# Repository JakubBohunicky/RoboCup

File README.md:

# RoboCup Junior Soccer

These are all the RoboCupJunior Soccer robots I built with my team, from our first Arduino Mega robot in 2024
to the two ESP32-S3 robots we took to the 2026 world final in Incheon.

| Folder | Event | Robot |
|---|---|---|
| [`2026_Korea/`](2026_Korea) | **RoboCup 2026 world final, Incheon: 11th of 24** | ESP32-S3, Maxon/ESCON drive, 48 line sensors, ESP-NOW role swapping ([write-up](https://developer.espressif.com/blog/2026/09/robocup-junior-soccer-robot/)) |
| [`2026_Slovakia/`](2026_Slovakia) | 2026 Slovak championship, 2nd place | Arduino Mega, gen 2 of the Bari robot |
| [`2025_Bari/`](2025_Bari) | RoboCup 2025, Bari | Arduino Mega, gen 1 |
| [`2024/`](2024) | RoboCup 2024, team XLC-Captur | Arduino Mega, our first robot |

**[2026_Korea](2026_Korea)** is the one we're proudest of.

Released under the [MIT License](LICENSE).

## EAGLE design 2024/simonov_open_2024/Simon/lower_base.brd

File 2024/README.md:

# RoboCupJunior Soccer 2024 — team XLC-Captur

This was our first RoboCupJunior Soccer robot. We built it around an **Arduino Mega**, with a BNO055
compass, a Pixy2 camera to find the goals, an SSD1306 display and a ring of TSOP IR receivers to find
the ball. We designed the electronics as three Eagle boards: a lower base, an upper base and the TSOP
sensor ring.

The firmware grew one sketch at a time, from `Code/MainCodeV1` to `Code/mainCodeV10`, which is the version
we ended with. Before putting each part into the main code, we tried it in a small sketch first: compass
rotation, dribbler, kicker, IR ball sensors and the Pixy. Those sketches are in `Code/test_code/`.

| Folder | Contents |
|---|---|
| `Code/` | Main firmware V1–V10 and the test sketches |
| `PCBs/` | Eagle schematics and boards |
| `Photo/` | Renders of the three boards |
| `Doc/` | Our team description paper, poster and BOM |

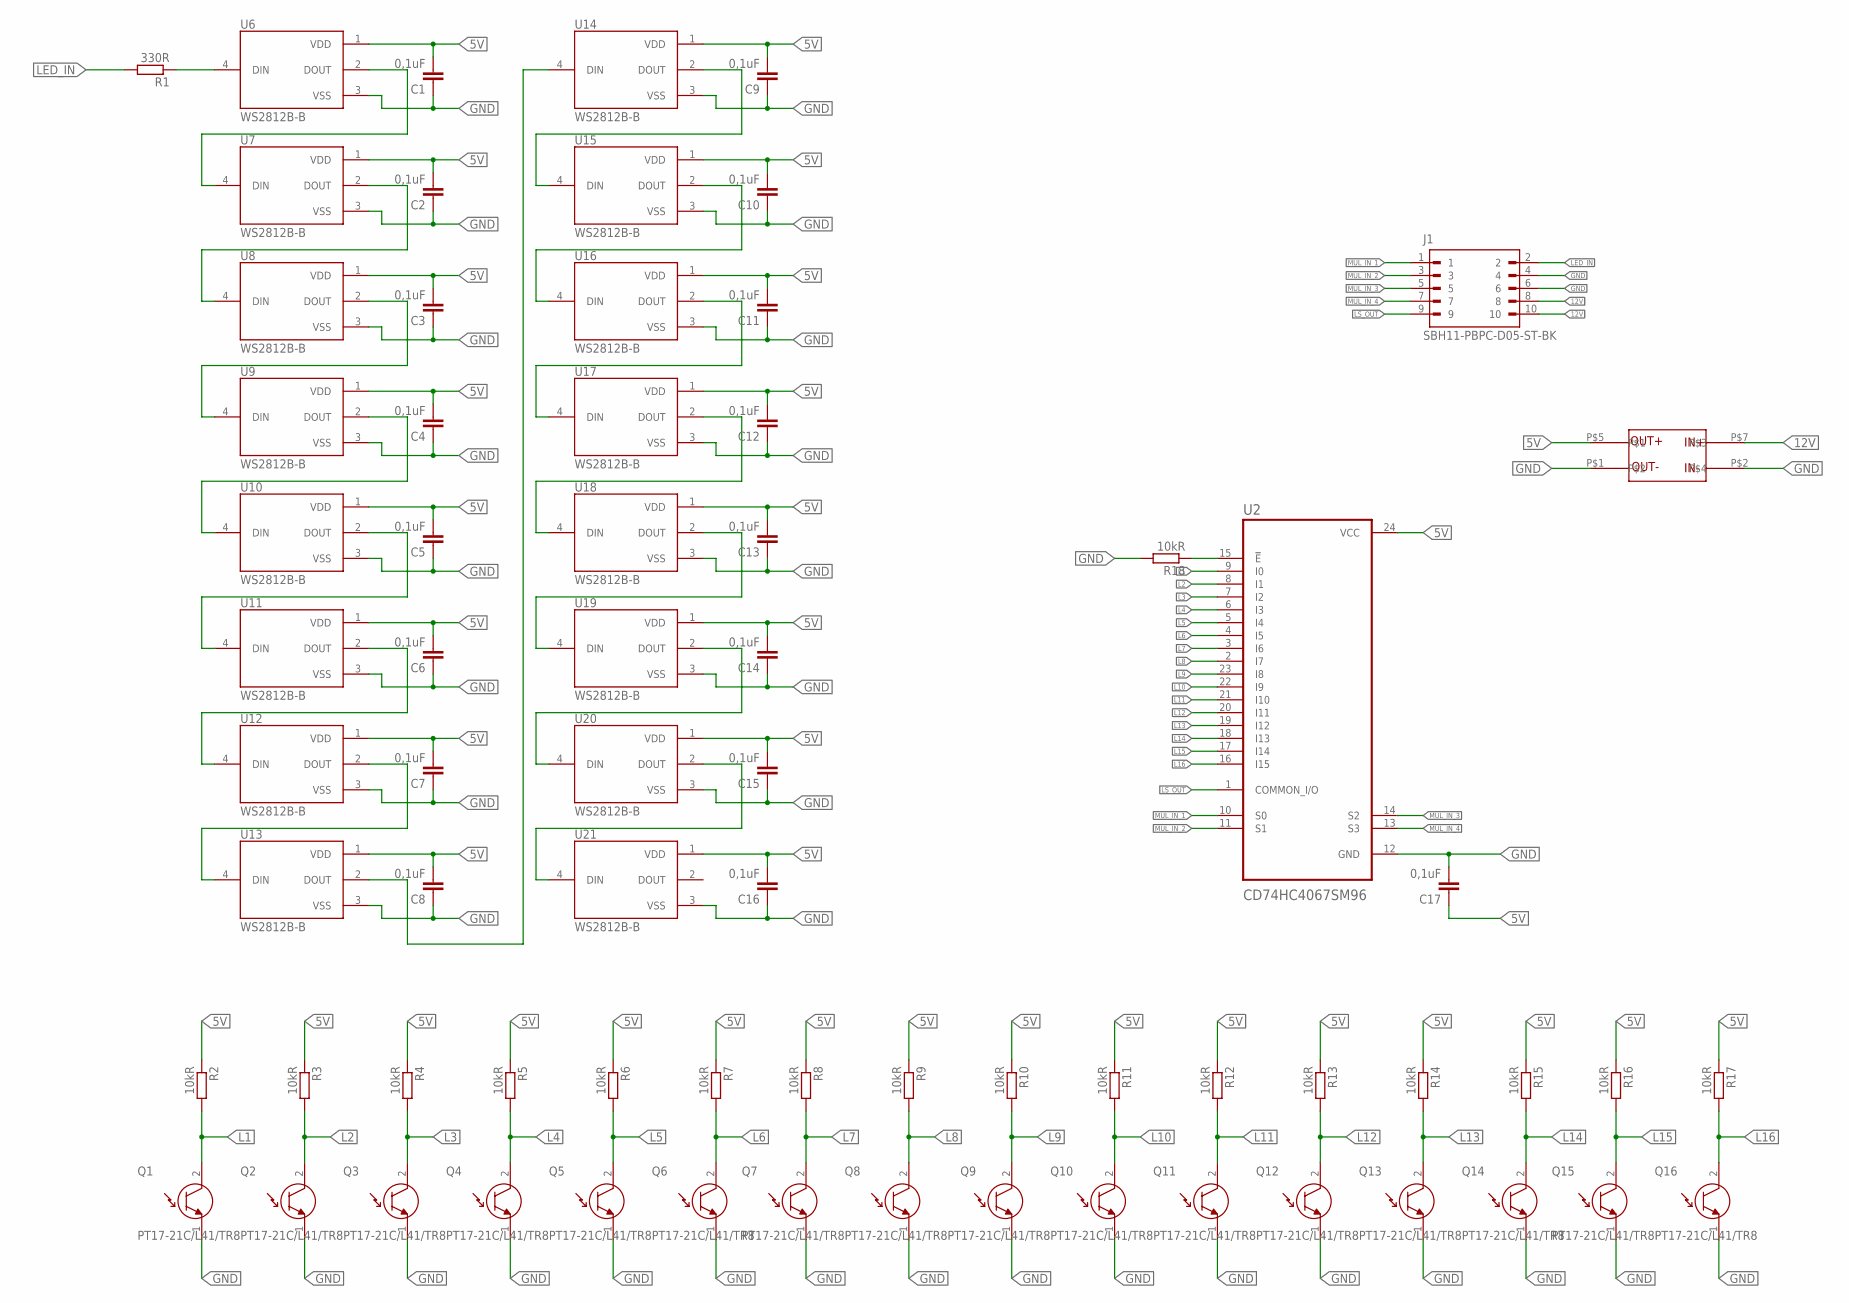
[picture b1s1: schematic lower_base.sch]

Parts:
C1, C2, C3, C4, C5, C6, C7, C8, C9, C10, C11, C12, C13, C14, C15, C16, C17: 0,1uF; C0805
J1: SBH11-PBPC-D05-ST-BK; SULLINS_SBH11-PBPC-D05-ST-BK
Q1, Q2, Q3, Q4, Q5, Q6, Q7, Q8, Q9, Q10, Q11, Q12, Q13, Q14, Q15, Q16: PT17-21C/L41/TR8; OPTO_PT17-21C/L41/TR8
R1: 330R; R0805
R2, R3, R4, R5, R6, R7, R8, R9, R10, R11, R12, R13, R14, R15, R16, R17, R18: 10kR; R0805
U2: CD74HC4067SM96; SOP65P780X200-24N
U6, U7, U8, U9, U10, U11, U12, U13, U14, U15, U16, U17, U18, U19, U20, U21: WS2812B-B; LED_WS2812B-B
U$1: REGULATOR_3A_MINI; REGULATOR_3A_MIN

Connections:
5V: C1.2, C2.2, C3.2, C4.2, C5.2, C6.2, C7.2, C8.2, C9.2, C10.2, C11.2, C12.2, C13.2, C14.2, C15.2, C16.2, C17.1, R2.1, R3.1, R4.1, R5.1, R6.1, R7.1, R8.1, R9.1, R10.1, R11.1, R12.1, R13.1, R14.1, R15.1, R16.1, R17.1, U2.24 (VCC), U6.1 (VDD), U7.1 (VDD), U8.1 (VDD), U9.1 (VDD), U10.1 (VDD), U11.1 (VDD), U12.1 (VDD), U13.1 (VDD), U14.1 (VDD), U15.1 (VDD), U16.1 (VDD), U17.1 (VDD), U18.1 (VDD), U19.1 (VDD), U20.1 (VDD), U21.1 (VDD), U$1.P$5
12V: J1.8, J1.10, U$1.P$7
GND: C1.1, C2.1, C3.1, C4.1, C5.1, C6.1, C7.1, C8.1, C9.1, C10.1, C11.1, C12.1, C13.1, C14.1, C15.1, C16.1, C17.2, J1.4, J1.6, Q1.1 (ET), Q2.1 (ET), Q3.1 (ET), Q4.1 (ET), Q5.1 (ET), Q6.1 (ET), Q7.1 (ET), Q8.1 (ET), Q9.1 (ET), Q10.1 (ET), Q11.1 (ET), Q12.1 (ET), Q13.1 (ET), Q14.1 (ET), Q15.1 (ET), Q16.1 (ET), R18.2, U2.12 (GND), U6.3 (VSS), U7.3 (VSS), U8.3 (VSS), U9.3 (VSS), U10.3 (VSS), U11.3 (VSS), U12.3 (VSS), U13.3 (VSS), U14.3 (VSS), U15.3 (VSS), U16.3 (VSS), U17.3 (VSS), U18.3 (VSS), U19.3 (VSS), U20.3 (VSS), U21.3 (VSS), U$1.P$1, U$1.P$2
L1: Q1.2 (CT), R2.2, U2.9 (I0)
L2: Q2.2 (CT), R3.2, U2.8 (I1)
L3: Q3.2 (CT), R4.2, U2.7 (I2)
L4: Q4.2 (CT), R5.2, U2.6 (I3)
L5: Q5.2 (CT), R6.2, U2.5 (I4)
L6: Q6.2 (CT), R7.2, U2.4 (I5)
L7: Q7.2 (CT), R8.2, U2.3 (I6)
L8: Q8.2 (CT), R9.2, U2.2 (I7)
L9: Q9.2 (CT), R10.2, U2.23 (I8)
L10: Q10.2 (CT), R11.2, U2.22 (I9)
L11: Q11.2 (CT), R12.2, U2.21 (I10)
L12: Q12.2 (CT), R13.2, U2.20 (I11)
L13: Q13.2 (CT), R14.2, U2.19 (I12)
L14: Q14.2 (CT), R15.2, U2.18 (I13)
L15: Q15.2 (CT), R16.2, U2.17 (I14)
L16: Q16.2 (CT), R17.2, U2.16 (I15)
LED_IN: J1.2, R1.2
LS_OUT: J1.9, U2.1 (COMMON_I/O)
MUL_IN_1: J1.1, U2.10 (S0)
MUL_IN_2: J1.3, U2.11 (S1)
MUL_IN_3: J1.5, U2.14 (S2)
MUL_IN_4: J1.7, U2.13 (S3)
unnamed: R1.1, U6.4 (DIN)
unnamed: U6.2 (DOUT), U7.4 (DIN)
unnamed: U7.2 (DOUT), U8.4 (DIN)
unnamed: U8.2 (DOUT), U9.4 (DIN)
unnamed: U9.2 (DOUT), U10.4 (DIN)
unnamed: U10.2 (DOUT), U11.4 (DIN)
unnamed: U11.2 (DOUT), U12.4 (DIN)
unnamed: U12.2 (DOUT), U13.4 (DIN)
unnamed: U13.2 (DOUT), U14.4 (DIN)
unnamed: U17.2 (DOUT), U18.4 (DIN)
unnamed: U18.2 (DOUT), U19.4 (DIN)
unnamed: U14.2 (DOUT), U15.4 (DIN)
unnamed: U15.2 (DOUT), U16.4 (DIN)
unnamed: U16.2 (DOUT), U17.4 (DIN)
unnamed: U19.2 (DOUT), U20.4 (DIN)
unnamed: U20.2 (DOUT), U21.4 (DIN)
unnamed: R18.1, U2.15 (!E)

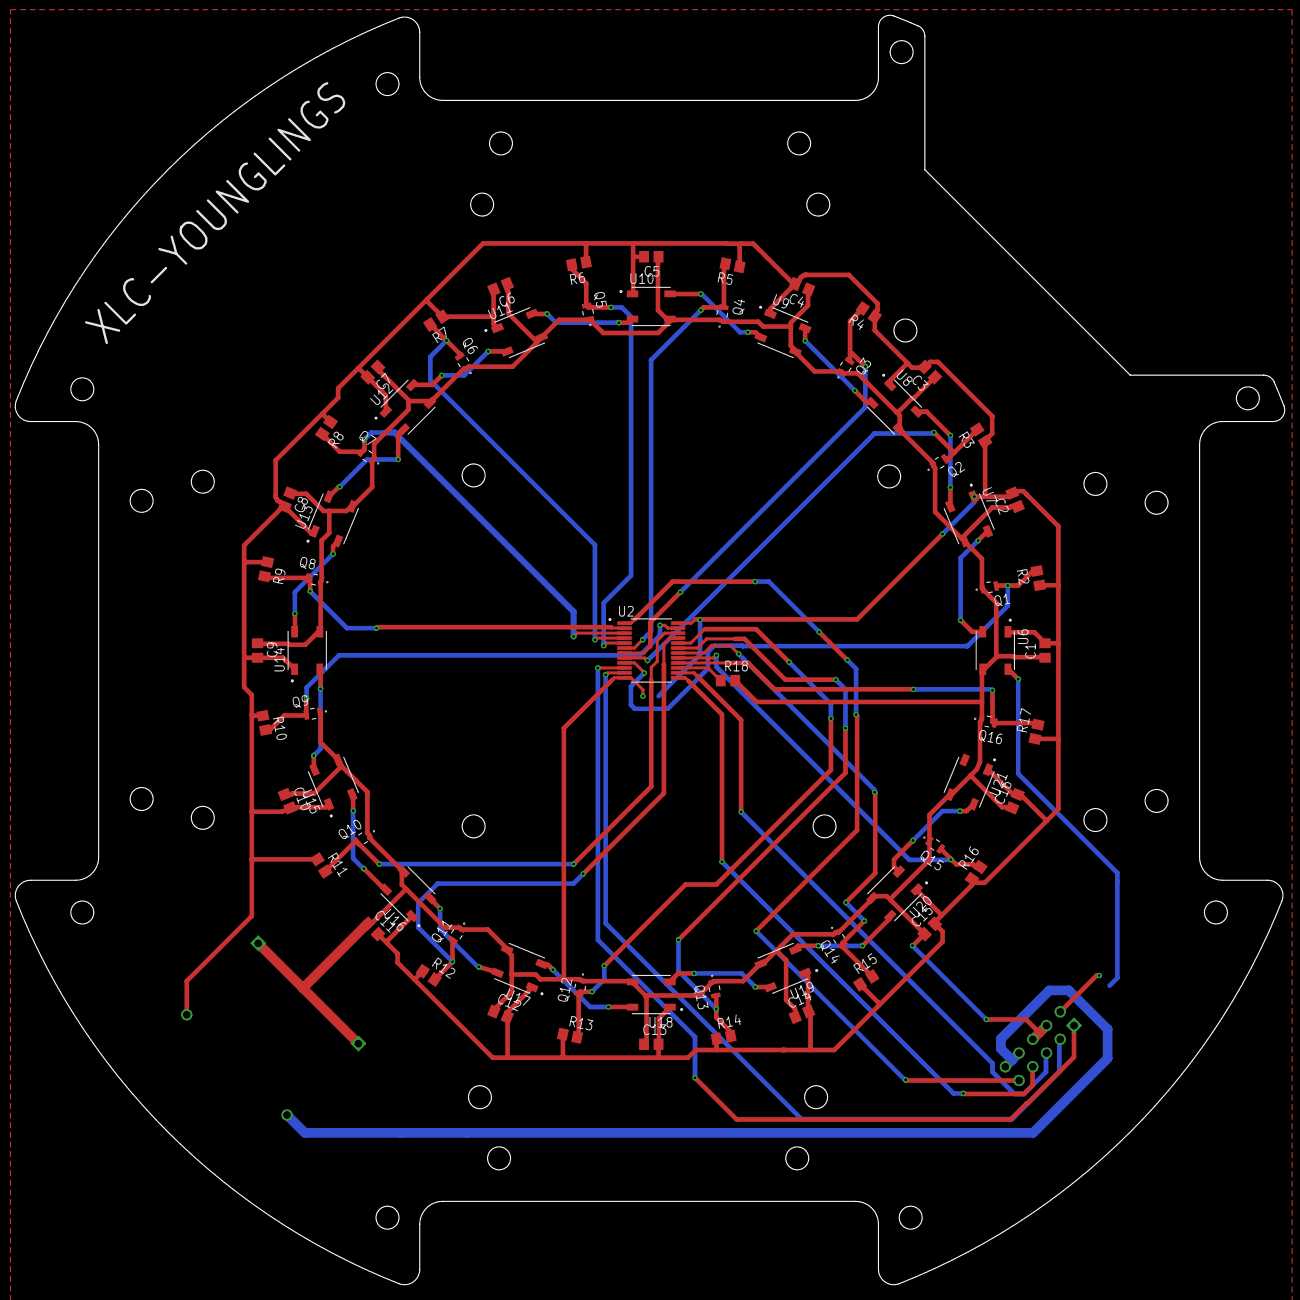
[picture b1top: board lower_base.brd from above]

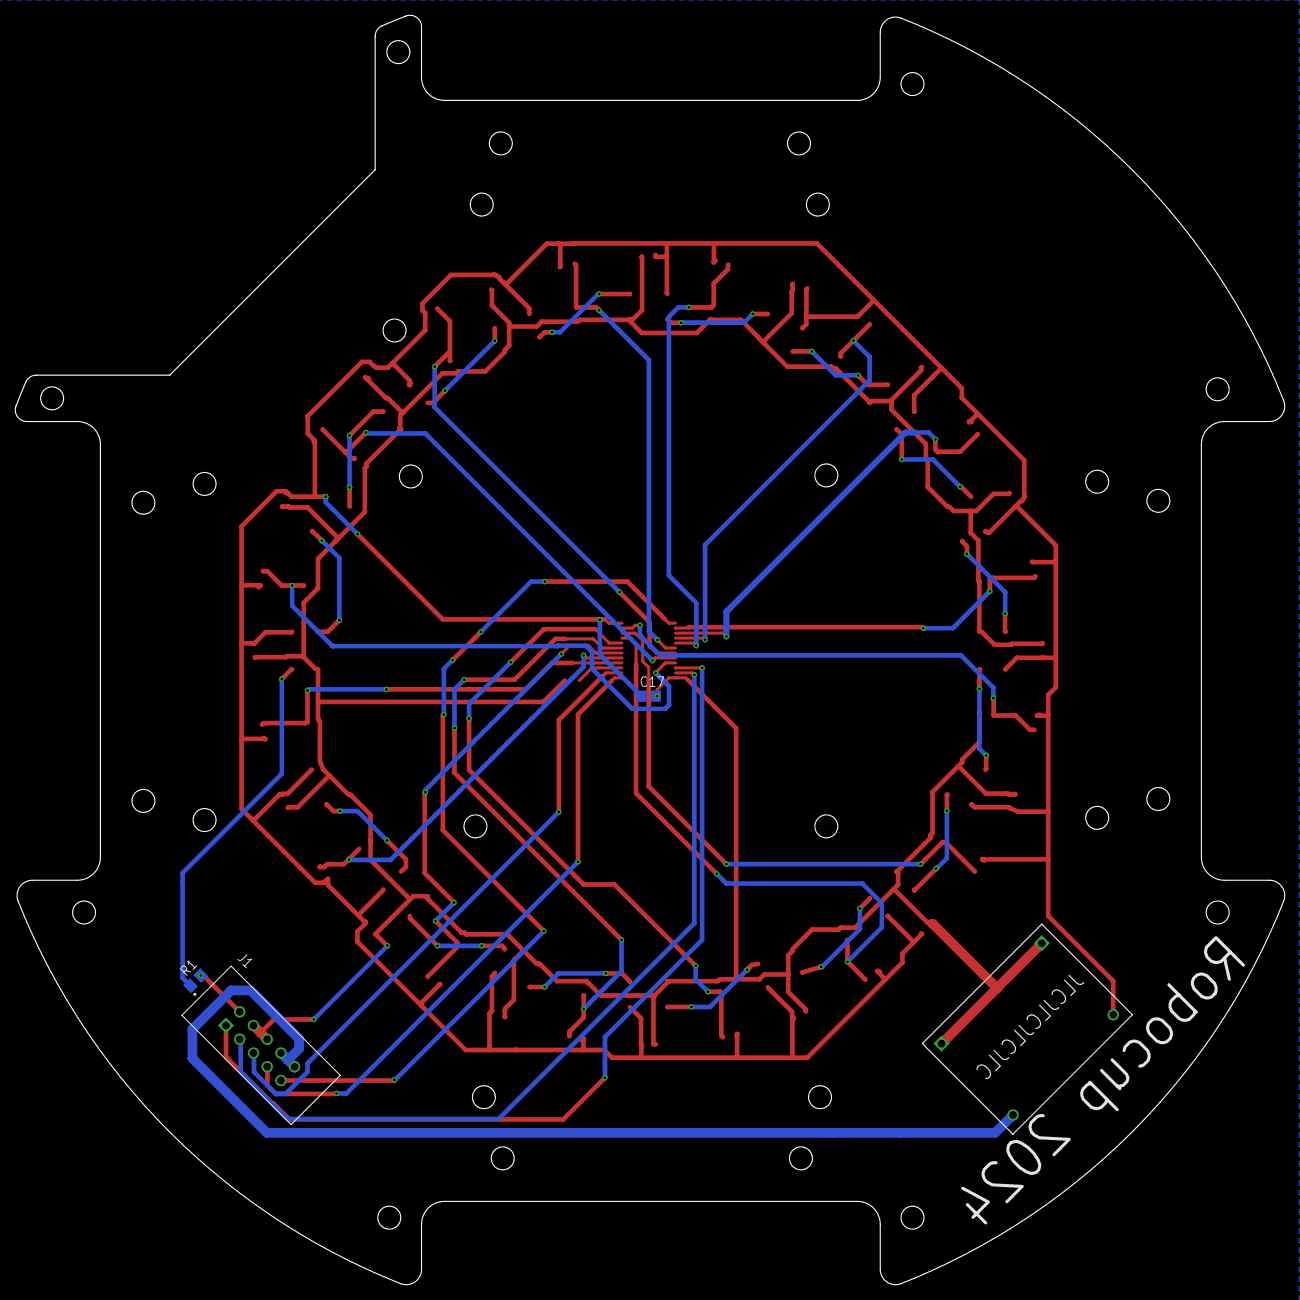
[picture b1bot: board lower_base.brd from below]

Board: 2 copper layers, 166.0 x 166.0 mm, 70 parts (4 on the bottom side), 42 nets.

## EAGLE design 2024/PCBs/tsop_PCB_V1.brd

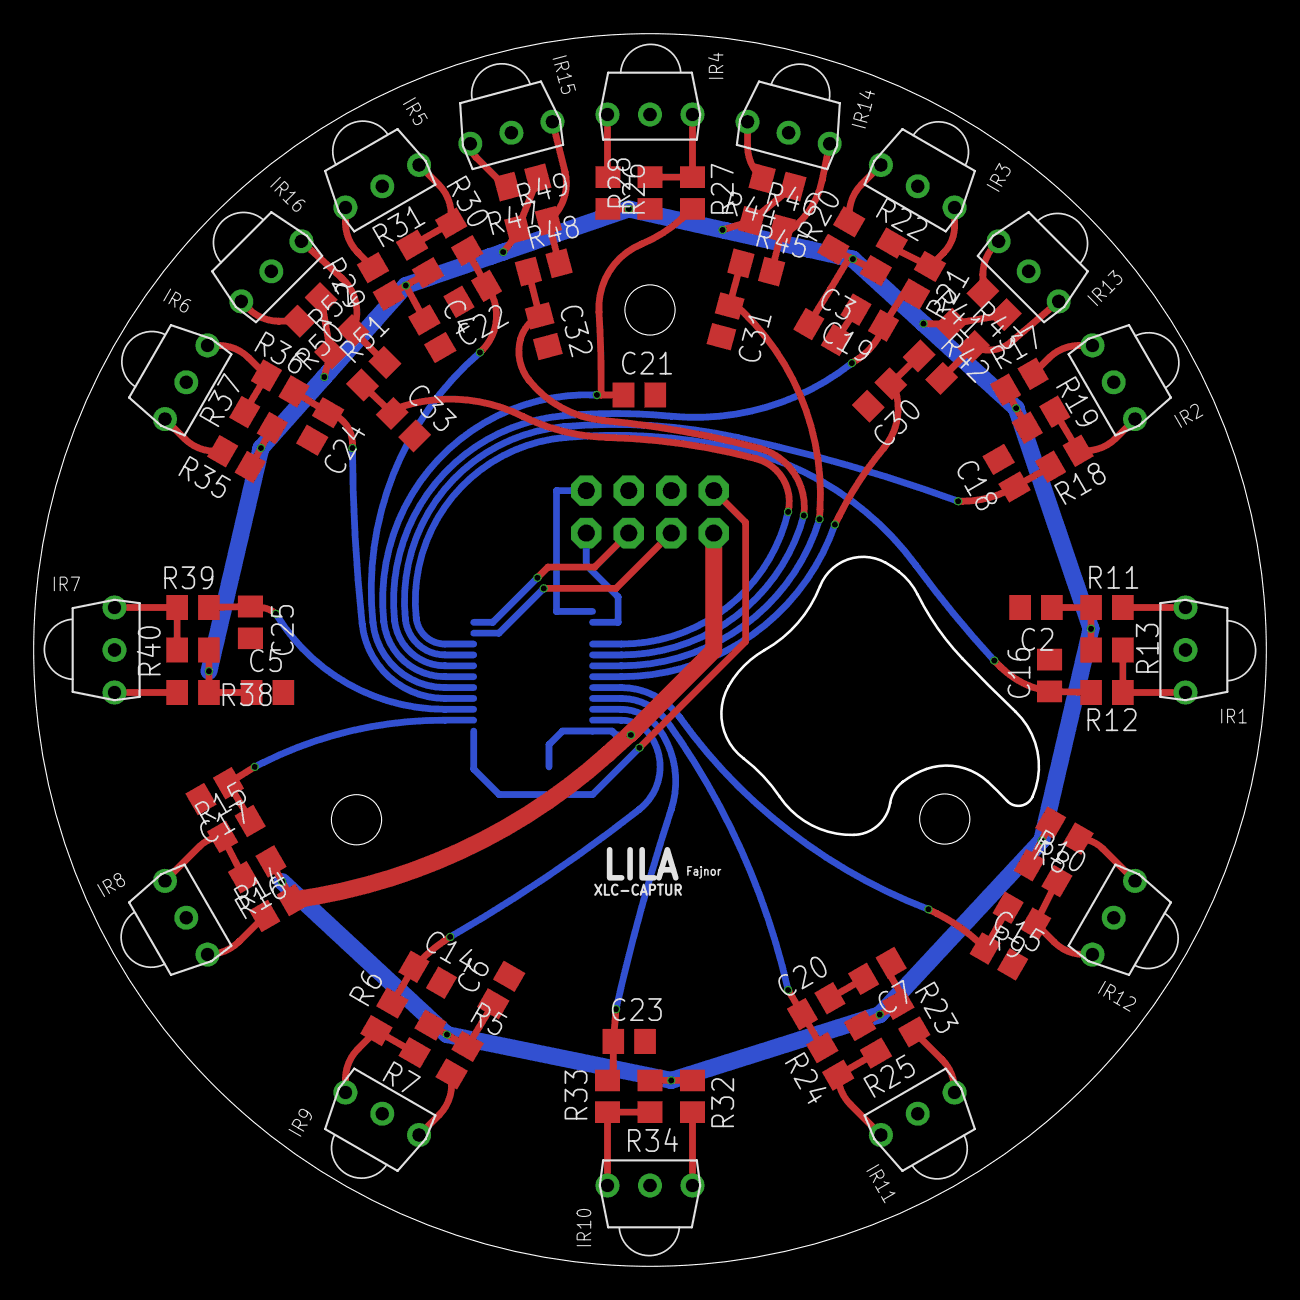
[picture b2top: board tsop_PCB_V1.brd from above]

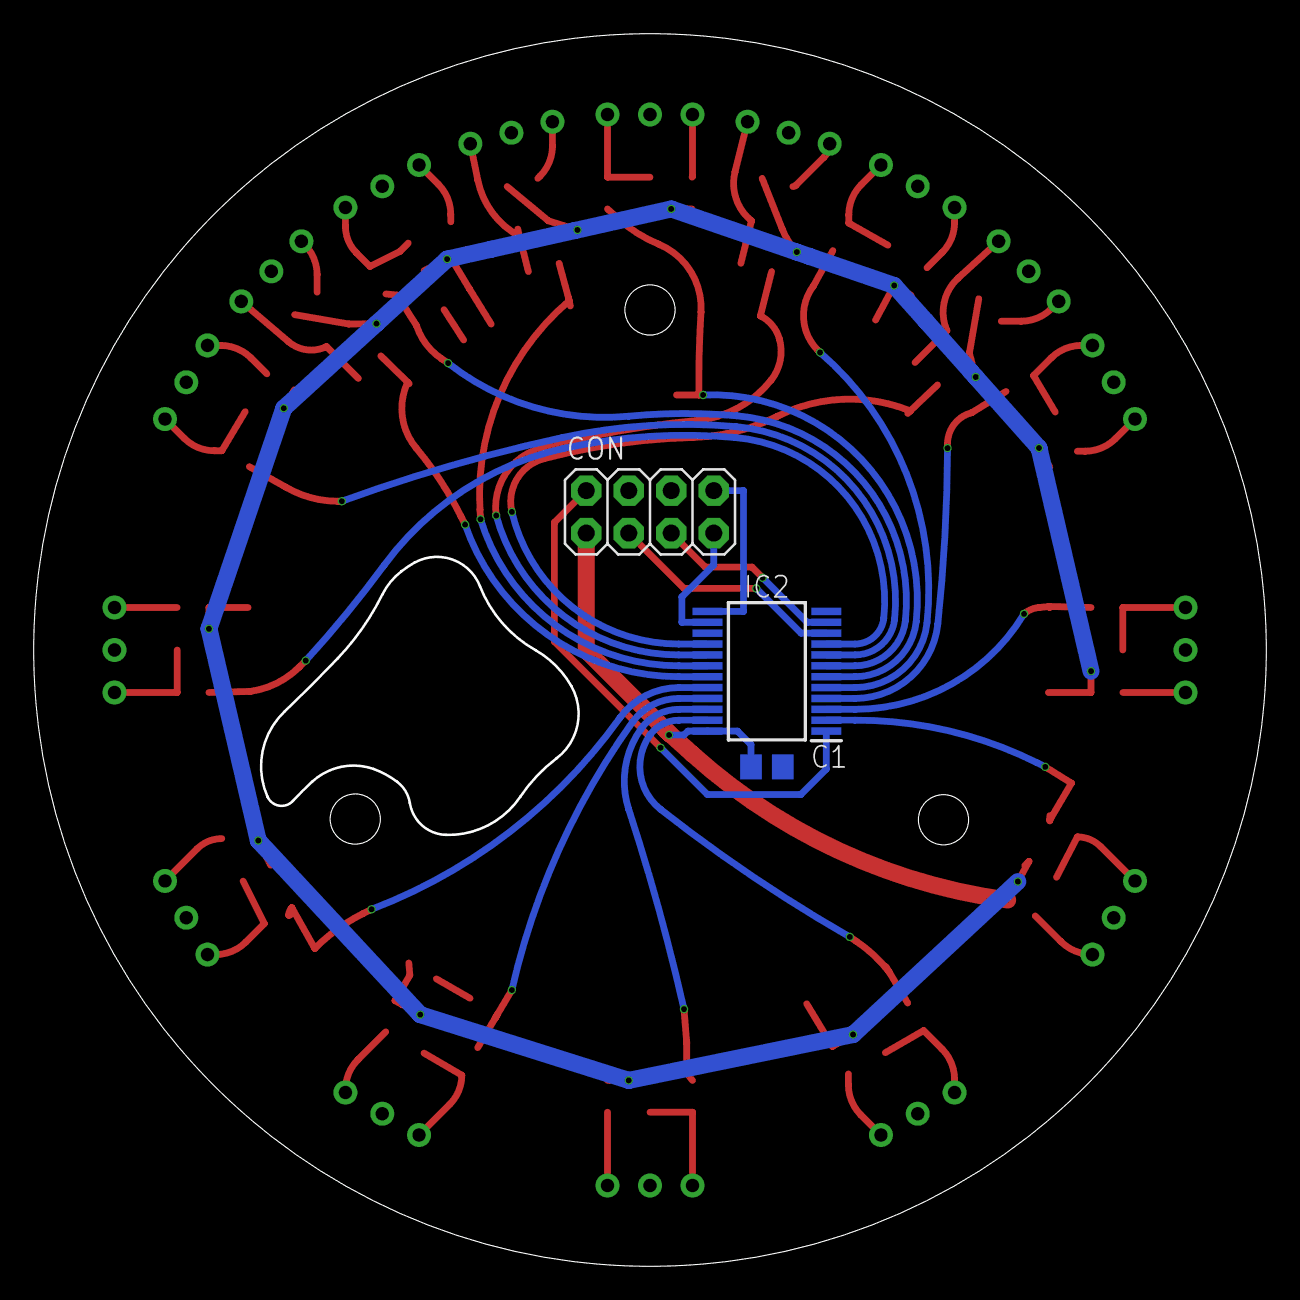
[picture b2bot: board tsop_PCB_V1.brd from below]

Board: 2 copper layers, 73.7 x 73.7 mm, 89 parts (3 on the bottom side), 55 nets.

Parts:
C1, C2, C3, C4, C5, C6, C7: 100nF; C0805
C14, C15, C16, C17, C18, C19, C20, C21, C22, C23, C24, C25, C30, C31, C32, C33: 1u; C0805
CON: 2X04
IC2: CD74HC4067SM96; SOP65P780X200-24N
IR1, IR2, IR3, IR4, IR5, IR6, IR7, IR8, IR9, IR10, IR11, IR12, IR13, IR14, IR15, IR16: TSSP58038; TSOP
R5, R8, R11, R14, R17, R20, R23, R26, R29, R32, R35, R38, R41, R44, R47, R50: 10R; R0805
R6, R9, R12, R15, R18, R21, R24, R27, R30, R33, R36, R39, R42, R45, R48, R51: 100k; R0805
R7, R10, R13, R16, R19, R22, R25, R28, R31, R34, R37, R40, R43, R46, R49, R52: 4.7k; R0805

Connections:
+5V: C1.1, C2.1, C3.1, C4.1, C5.1, C6.1, C7.1, CON.1, IC2.24, R5.1, R7.1, R8.1, R10.1, R11.1, R13.1, R14.1, R16.1, R17.1, R19.1, R20.1, R22.1, R23.1, R25.1, R26.1, R28.1, R29.1, R31.1, R32.1, R34.1, R35.1, R37.1, R38.1, R40.1, R41.1, R43.1, R44.1, R46.1, R47.1, R49.1, R50.1, R52.1
GND: C1.2, C2.2, C3.2, C4.2, C5.2, C6.2, C7.2, C14.2, C15.2, C16.2, C17.2, C18.2, C19.2, C20.2, C21.2, C22.2, C23.2, C24.2, C25.2, C30.2, C31.2, C32.2, C33.2, CON.6, IC2.12, IC2.15, IR1.GND, IR2.GND, IR3.GND, IR4.GND, IR5.GND, IR6.GND, IR7.GND, IR8.GND, IR9.GND, IR10.GND, IR11.GND, IR12.GND, IR13.GND, IR14.GND, IR15.GND, IR16.GND
I0: C16.1, IC2.9, R12.1
I1: C18.1, IC2.8, R18.1
I2: C19.1, IC2.7, R21.1
I3: C21.1, IC2.6, R27.1
I4: C22.1, IC2.5, R30.1
I5: C24.1, IC2.4, R36.1
I6: C25.1, IC2.3, R39.1
I7: C17.1, IC2.2, R15.1
I8: C14.1, IC2.23, R6.1
I9: C23.1, IC2.22, R33.1
I10: C20.1, IC2.21, R24.1
I11: C15.1, IC2.20, R9.1
I12: C30.1, IC2.19, R42.1
I13: C31.1, IC2.18, R45.1
I14: C32.1, IC2.17, R48.1
I15: C33.1, IC2.16, R51.1
IR_READ: CON.2, IC2.1
LIGHT_SET_0: CON.3, IC2.10
LIGHT_SET_1: CON.5, IC2.11
LIGHT_SET_2: CON.7, IC2.14
LIGHT_SET_3: CON.8, IC2.13
unnamed: IR12.VS, R8.2
unnamed: IR1.VS, R11.2
unnamed: IR8.VS, R14.2
unnamed: IR2.VS, R17.2
unnamed: IR3.VS, R20.2
unnamed: IR11.VS, R23.2
unnamed: IR4.VS, R26.2
unnamed: IR5.VS, R29.2
unnamed: IR10.VS, R32.2
unnamed: IR9.VS, R5.2
unnamed: IR6.VS, R35.2
unnamed: IR7.VS, R38.2
unnamed: IR12.VO, R9.2, R10.2
unnamed: IR9.VO, R6.2, R7.2
unnamed: IR5.VO, R30.2, R31.2
unnamed: IR1.VO, R12.2, R13.2
unnamed: IR13.VS, R41.2
unnamed: IR8.VO, R15.2, R16.2
unnamed: IR4.VO, R27.2, R28.2
unnamed: IR2.VO, R18.2, R19.2
unnamed: IR14.VS, R44.2
unnamed: IR11.VO, R24.2, R25.2
unnamed: IR3.VO, R21.2, R22.2
unnamed: IR15.VS, R47.2
unnamed: IR10.VO, R33.2, R34.2
unnamed: IR16.VS, R50.2
unnamed: IR6.VO, R36.2, R37.2
unnamed: IR13.VO, R42.2, R43.2
unnamed: IR7.VO, R39.2, R40.2
unnamed: IR14.VO, R45.2, R46.2
unnamed: IR15.VO, R48.2, R49.2
unnamed: IR16.VO, R51.2, R52.2

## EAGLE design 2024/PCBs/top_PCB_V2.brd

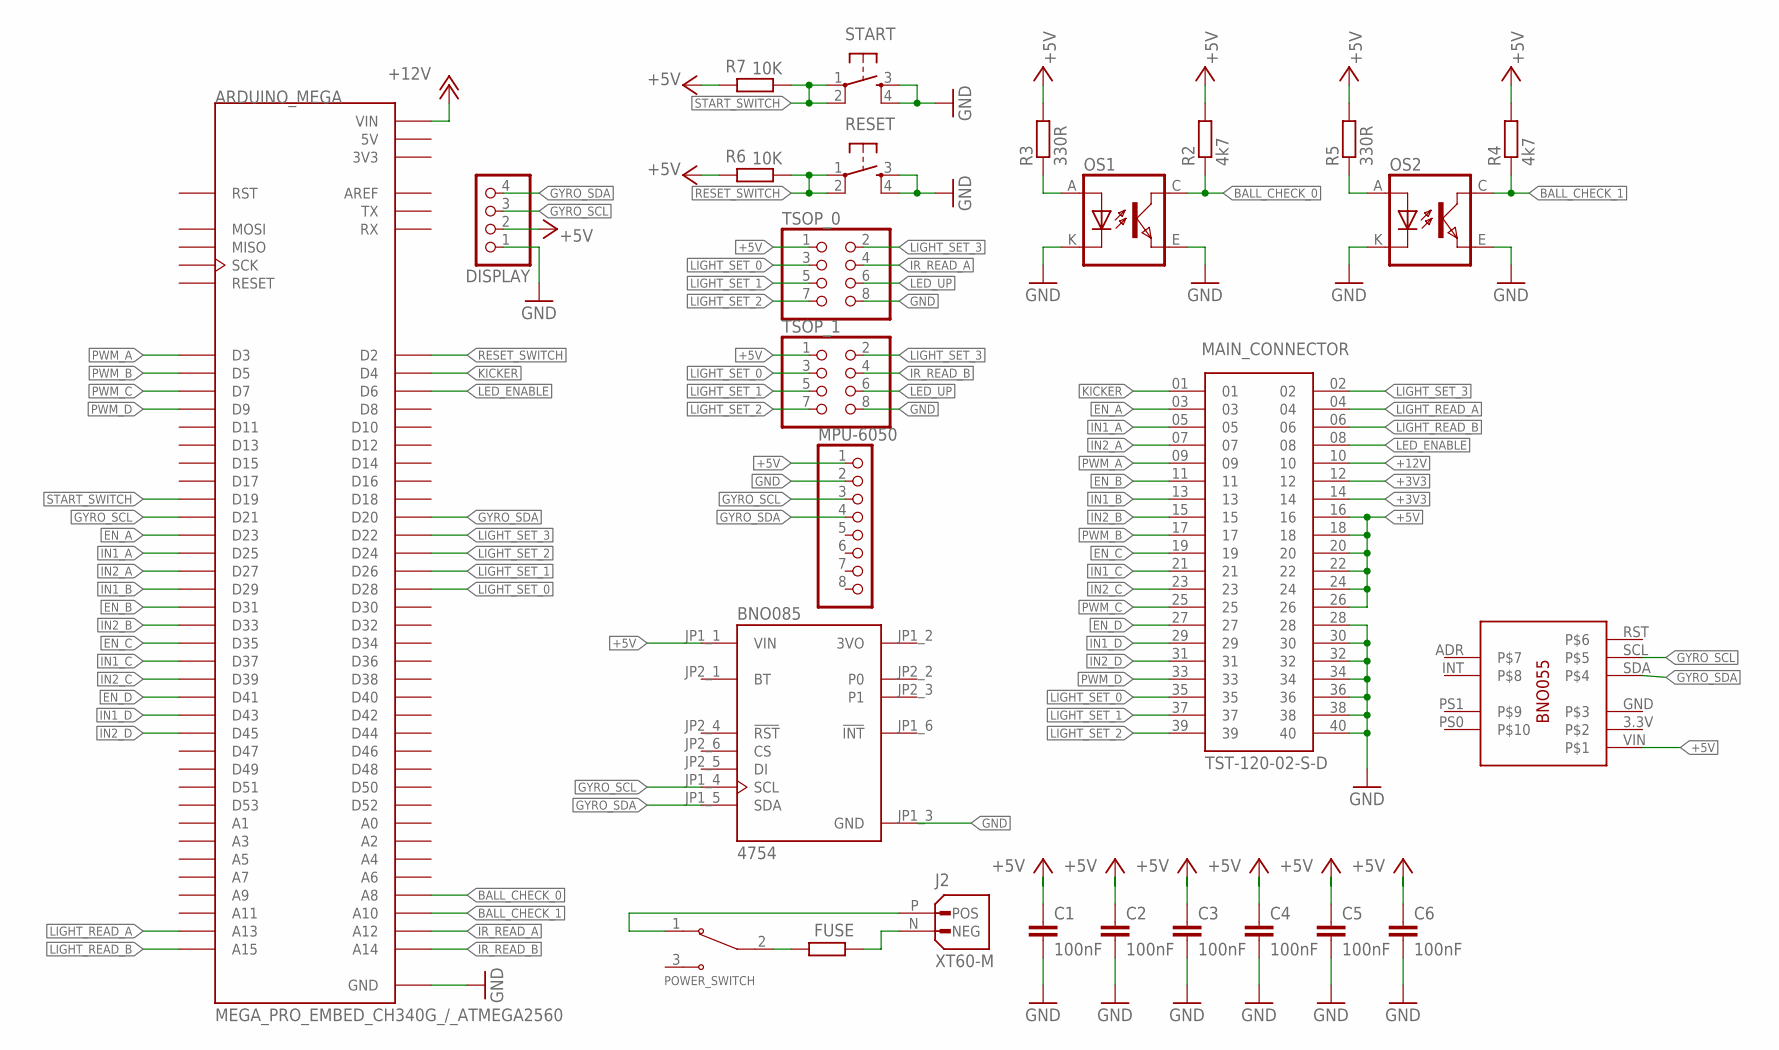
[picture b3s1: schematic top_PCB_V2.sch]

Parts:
ARDUINO_MEGA: MEGA_PRO_EMBED_CH340G_/_ATMEGA2560; MODULE_MEGA_PRO_EMBED_CH340G_/_ATMEGA2560
BNO085: 4754; MODULE_4754
C1, C2, C3, C4, C5, C6: 100nF; C0805
DISPLAY: PINHD-1X4; 1X04
FUSE: R-EU_R1206; R1206
J2: XT60-M; AMASS_XT60-M
MAIN_CONNECTOR: TST-120-02-S-D; SAMTEC_TST-120-02-S-D
MPU-6050: PINHD-1X8; 1X08
OS1, OS2: TCRT5000
POWER_SWITCH: 100SP1T1B4M2QE; SW_100SP1T1B4M2QE
R2, R4: 4k7; R1206
R3, R5: 330R; R1206
R6, R7: 10K; R1206
RESET: DTSM-6
START: DTSM-6
TSOP_0, TSOP_1: PINHD-2X4; 2X04
U$1: BNO055_ADAFRUIT; BNO055

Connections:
3V3: ARDUINO_MEGA.3V3_1 (3V3), ARDUINO_MEGA.3V3_2 (3V3)
5V: ARDUINO_MEGA.5V_1 (5V), ARDUINO_MEGA.5V_2 (5V), ARDUINO_MEGA.5V_3 (5V)
+3V3: MAIN_CONNECTOR.12, MAIN_CONNECTOR.14
+5V: BNO085.JP1_1 (VIN), C1.1, C2.1, C3.1, C4.1, C5.1, C6.1, DISPLAY.2, MAIN_CONNECTOR.16, MAIN_CONNECTOR.18, MAIN_CONNECTOR.20, MAIN_CONNECTOR.22, MAIN_CONNECTOR.24, MAIN_CONNECTOR.26, MPU-6050.1, R2.2, R3.2, R4.2, R5.2, R6.2, R7.2, TSOP_0.1, TSOP_1.1, U$1.VIN
+12V: ARDUINO_MEGA.VIN_1 (VIN), ARDUINO_MEGA.VIN_2 (VIN), MAIN_CONNECTOR.10
BALL_CHECK_0: ARDUINO_MEGA.A8, OS1.C (COLLECTOR), R2.1
BALL_CHECK_1: ARDUINO_MEGA.A10, OS2.C (COLLECTOR), R4.1
EN_A: ARDUINO_MEGA.D23, MAIN_CONNECTOR.03
EN_B: ARDUINO_MEGA.D31, MAIN_CONNECTOR.11
EN_C: ARDUINO_MEGA.D35, MAIN_CONNECTOR.19
EN_D: ARDUINO_MEGA.D41, MAIN_CONNECTOR.27
GND: ARDUINO_MEGA.GND_1 (GND), ARDUINO_MEGA.GND_2 (GND), ARDUINO_MEGA.GND_3 (GND), BNO085.JP1_3 (GND), C1.2, C2.2, C3.2, C4.2, C5.2, C6.2, DISPLAY.1, MAIN_CONNECTOR.28, MAIN_CONNECTOR.30, MAIN_CONNECTOR.32, MAIN_CONNECTOR.34, MAIN_CONNECTOR.36, MAIN_CONNECTOR.38, MAIN_CONNECTOR.40, MPU-6050.2, OS1.E (EMITTER), OS1.K (CATHODE), OS2.E (EMITTER), OS2.K (CATHODE), RESET.3, RESET.4, START.3, START.4, TSOP_0.8, TSOP_1.8
GYRO_SCL: ARDUINO_MEGA.D21, BNO085.JP1_4 (SCL), DISPLAY.3, MPU-6050.3, U$1.SCL
GYRO_SDA: ARDUINO_MEGA.D20, BNO085.JP1_5 (SDA), DISPLAY.4, MPU-6050.4, U$1.SDA
IN1_A: ARDUINO_MEGA.D25, MAIN_CONNECTOR.05
IN1_B: ARDUINO_MEGA.D29, MAIN_CONNECTOR.13
IN1_C: ARDUINO_MEGA.D37, MAIN_CONNECTOR.21
IN1_D: ARDUINO_MEGA.D43, MAIN_CONNECTOR.29
IN2_A: ARDUINO_MEGA.D27, MAIN_CONNECTOR.07
IN2_B: ARDUINO_MEGA.D33, MAIN_CONNECTOR.15
IN2_C: ARDUINO_MEGA.D39, MAIN_CONNECTOR.23
IN2_D: ARDUINO_MEGA.D45, MAIN_CONNECTOR.31
IR_READ_A: ARDUINO_MEGA.A12, TSOP_0.4
IR_READ_B: ARDUINO_MEGA.A14, TSOP_1.4
KICKER: ARDUINO_MEGA.D4, MAIN_CONNECTOR.01
LED_ENABLE: ARDUINO_MEGA.D6, MAIN_CONNECTOR.08
LED_UP: TSOP_0.6, TSOP_1.6
LIGHT_READ_A: ARDUINO_MEGA.A13, MAIN_CONNECTOR.04
LIGHT_READ_B: ARDUINO_MEGA.A15, MAIN_CONNECTOR.06
LIGHT_SET_0: ARDUINO_MEGA.D28, MAIN_CONNECTOR.35, TSOP_0.3, TSOP_1.3
LIGHT_SET_1: ARDUINO_MEGA.D26, MAIN_CONNECTOR.37, TSOP_0.5, TSOP_1.5
LIGHT_SET_2: ARDUINO_MEGA.D24, MAIN_CONNECTOR.39, TSOP_0.7, TSOP_1.7
LIGHT_SET_3: ARDUINO_MEGA.D22, MAIN_CONNECTOR.02, TSOP_0.2, TSOP_1.2
unnamed: FUSE.2, POWER_SWITCH.2
unnamed: J2.P (POS), POWER_SWITCH.1
unnamed: FUSE.1, J2.N (NEG)
unnamed: OS2.A (ANODE), R5.1
unnamed: OS1.A (ANODE), R3.1
PWM_A: ARDUINO_MEGA.D3, MAIN_CONNECTOR.09
PWM_B: ARDUINO_MEGA.D5, MAIN_CONNECTOR.17
PWM_C: ARDUINO_MEGA.D7, MAIN_CONNECTOR.25
PWM_D: ARDUINO_MEGA.D9, MAIN_CONNECTOR.33
RESET_SWITCH: ARDUINO_MEGA.D2, R6.1, RESET.1, RESET.2
START_SWITCH: ARDUINO_MEGA.D19, R7.1, START.1, START.2

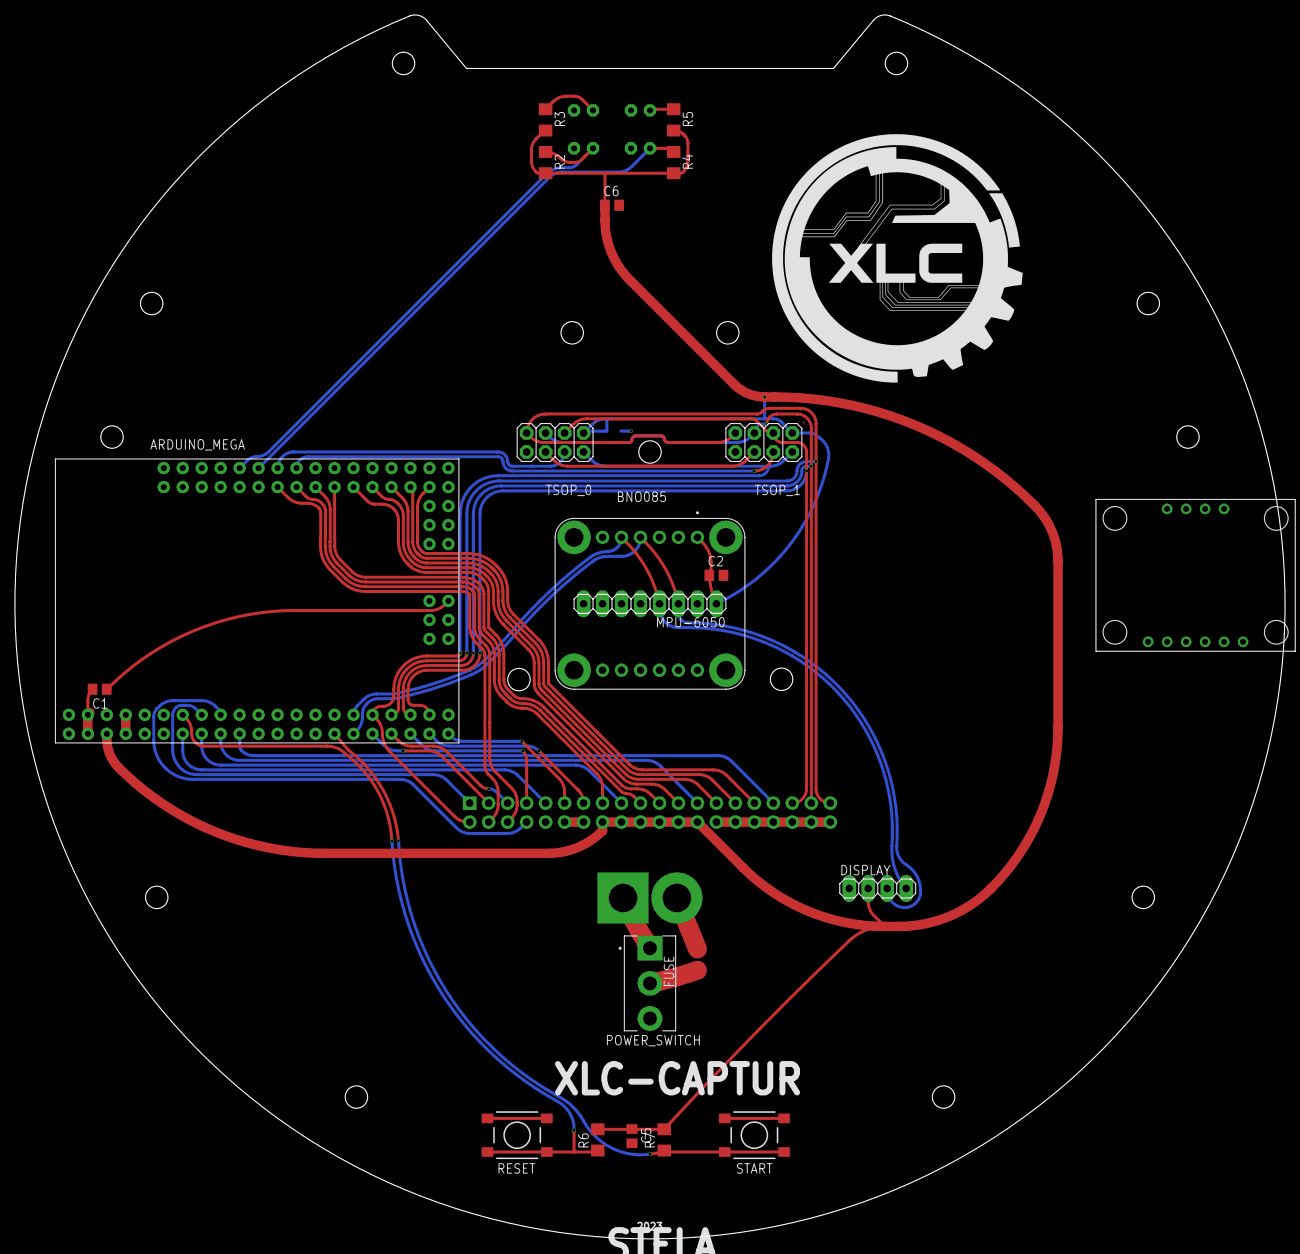
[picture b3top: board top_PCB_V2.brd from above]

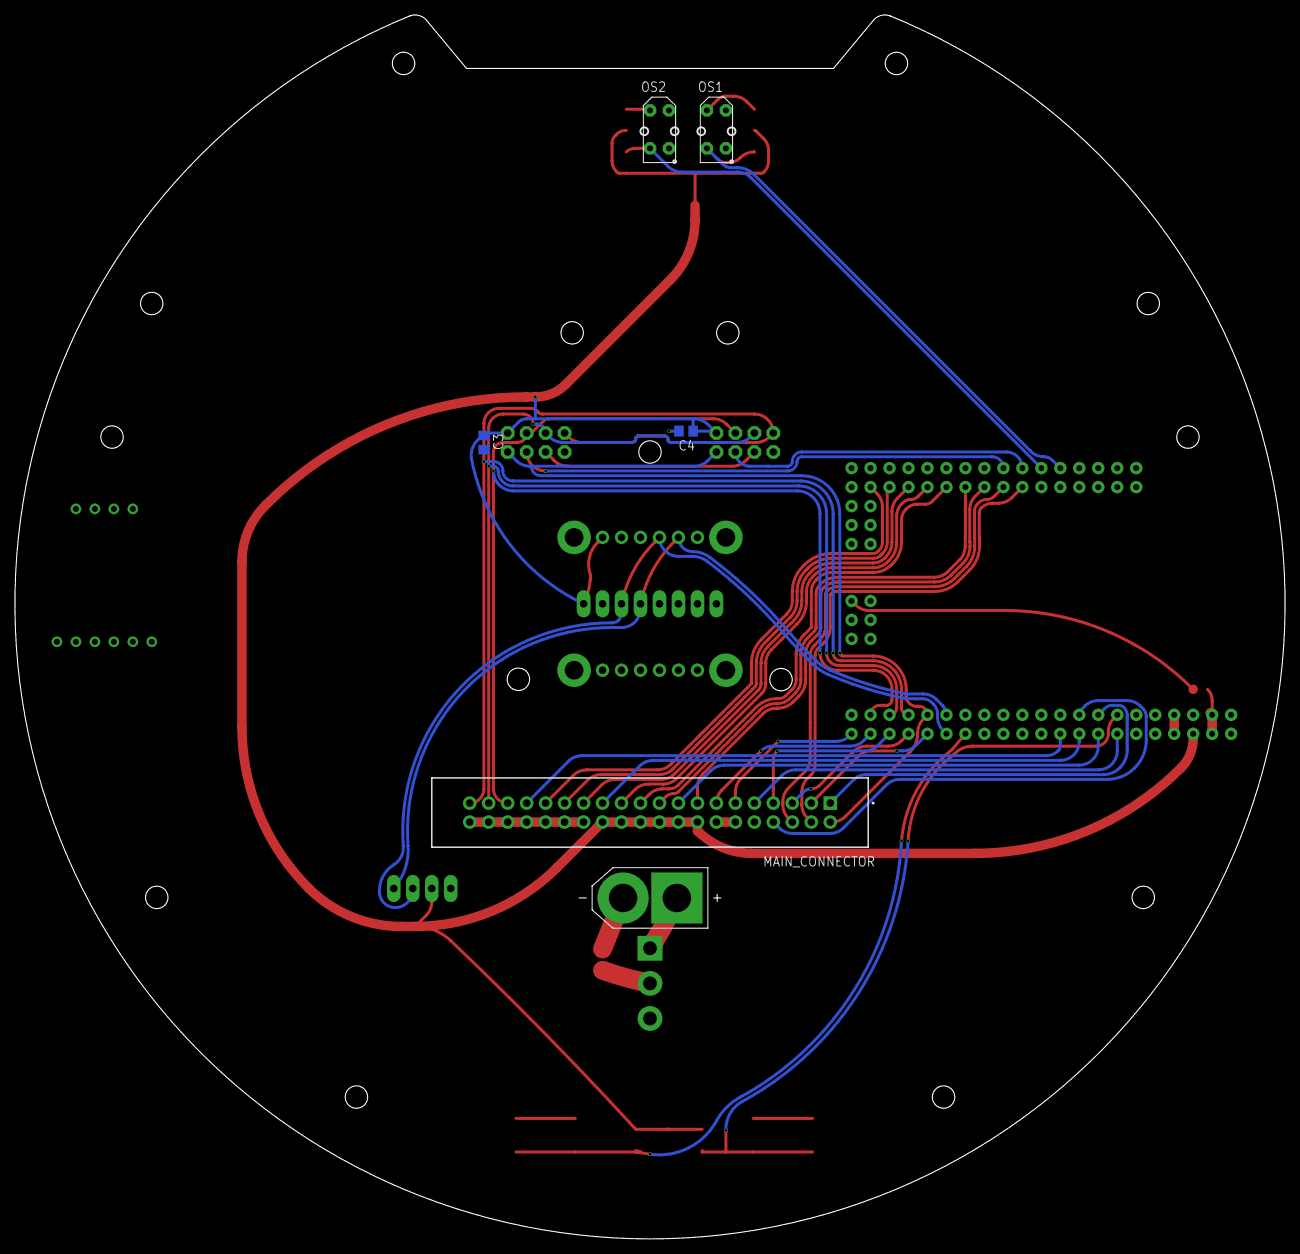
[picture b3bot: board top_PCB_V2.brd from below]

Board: 2 copper layers, 170.0 x 163.8 mm, 27 parts (6 on the bottom side), 44 nets.
